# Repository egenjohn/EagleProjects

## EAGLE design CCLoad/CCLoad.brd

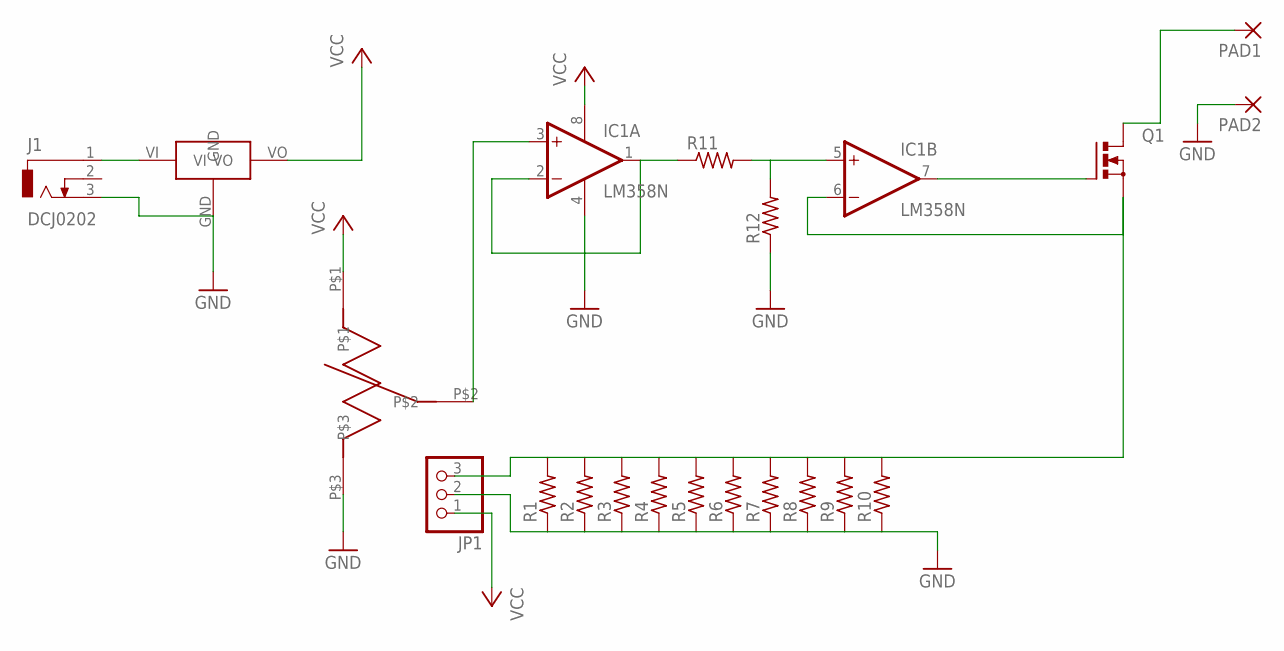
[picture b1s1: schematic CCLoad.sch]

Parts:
IC1: LM358N; DIL08
J1: DCJ0202
JP1: PINHD-1X3; 1X03
PAD1, PAD2: 3,17/1,3
Q1: PMOSFET_NTO220BV; TO220BV
R1, R2, R3, R4, R5, R6, R7, R8, R9, R10, R11, R12: R-US_0207/10; 0207/10
U$1: 3590
U$3: 7805-TO220V; TO220AV

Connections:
GND: IC1.4 (V-), J1.3, JP1.2, PAD2.1, R1.1, R2.1, R3.1, R4.1, R5.1, R6.1, R7.1, R8.1, R9.1, R10.1, R12.1, U$1.P$3, U$3.GND
unnamed: IC1.1 (OUT), IC1.2 (-IN), R11.1
unnamed: IC1.5 (+IN), R11.2, R12.2
unnamed: IC1.7 (OUT), Q1.G
unnamed: IC1.6 (-IN), JP1.3, Q1.S, R1.2, R2.2, R3.2, R4.2, R5.2, R6.2, R7.2, R8.2, R9.2, R10.2
unnamed: PAD1.1, Q1.D
unnamed: J1.1, U$3.VI
unnamed: IC1.3 (+IN), U$1.P$2
VCC: IC1.8 (V+), JP1.1, U$1.P$1, U$3.VO

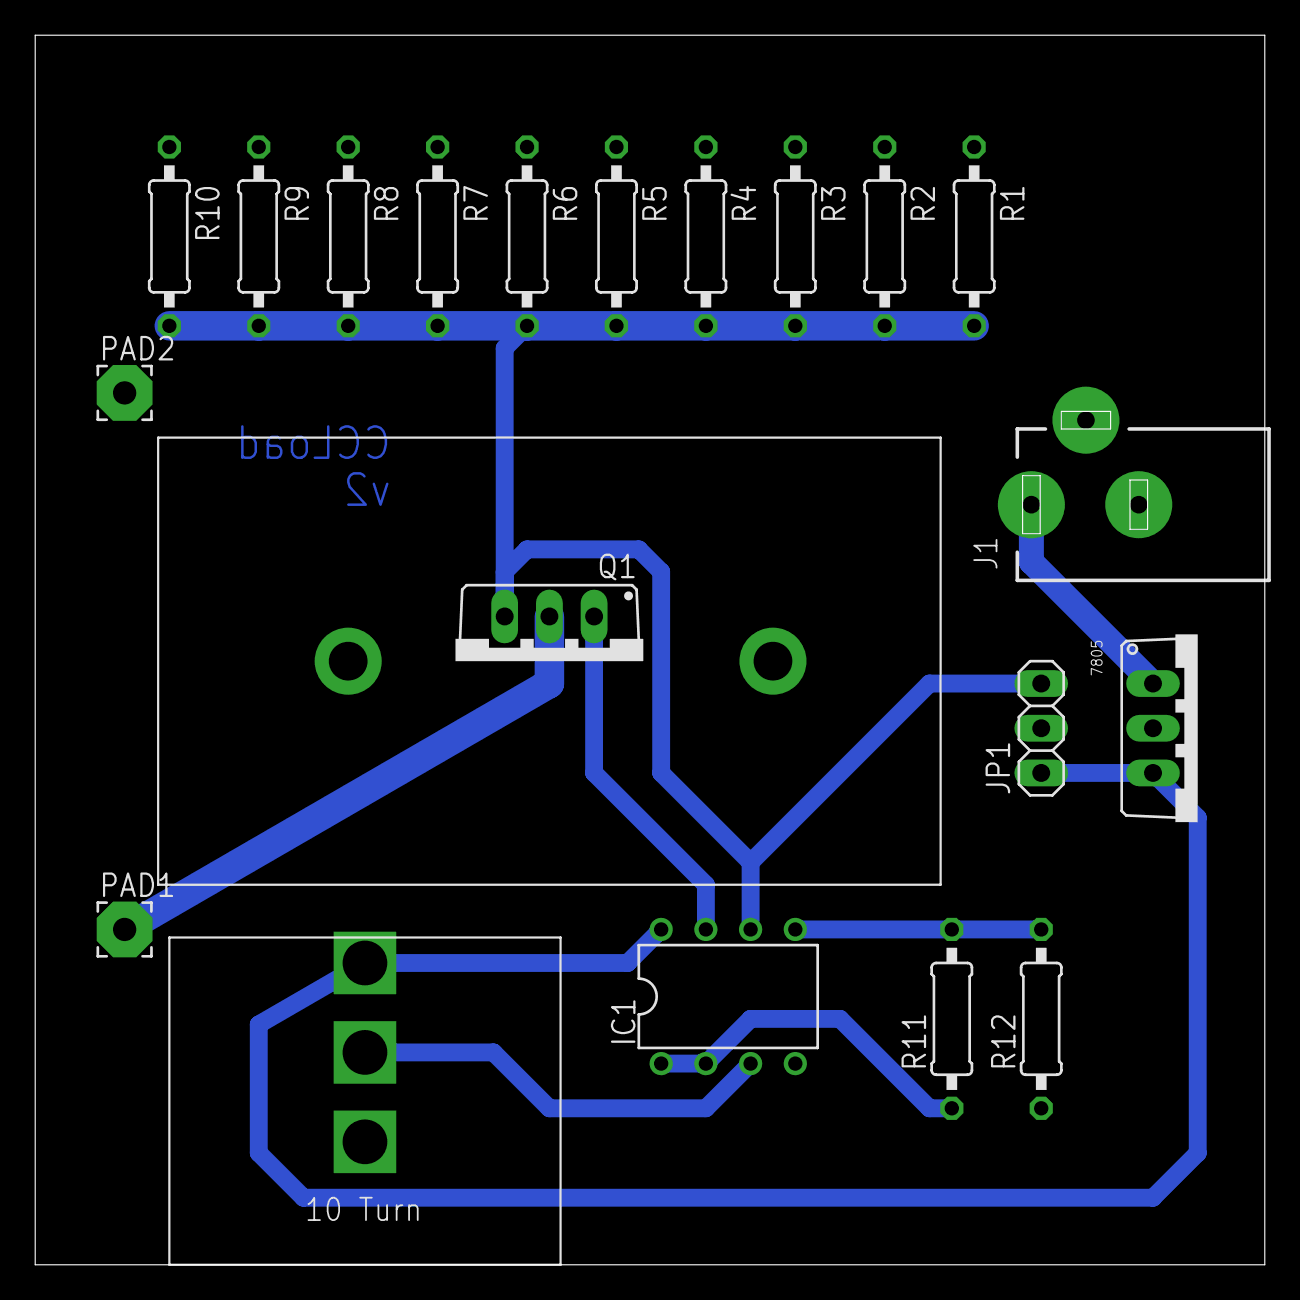
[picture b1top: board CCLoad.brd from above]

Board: 2 copper layers, 69.8 x 69.8 mm, 20 parts (0 on the bottom side), 9 nets.

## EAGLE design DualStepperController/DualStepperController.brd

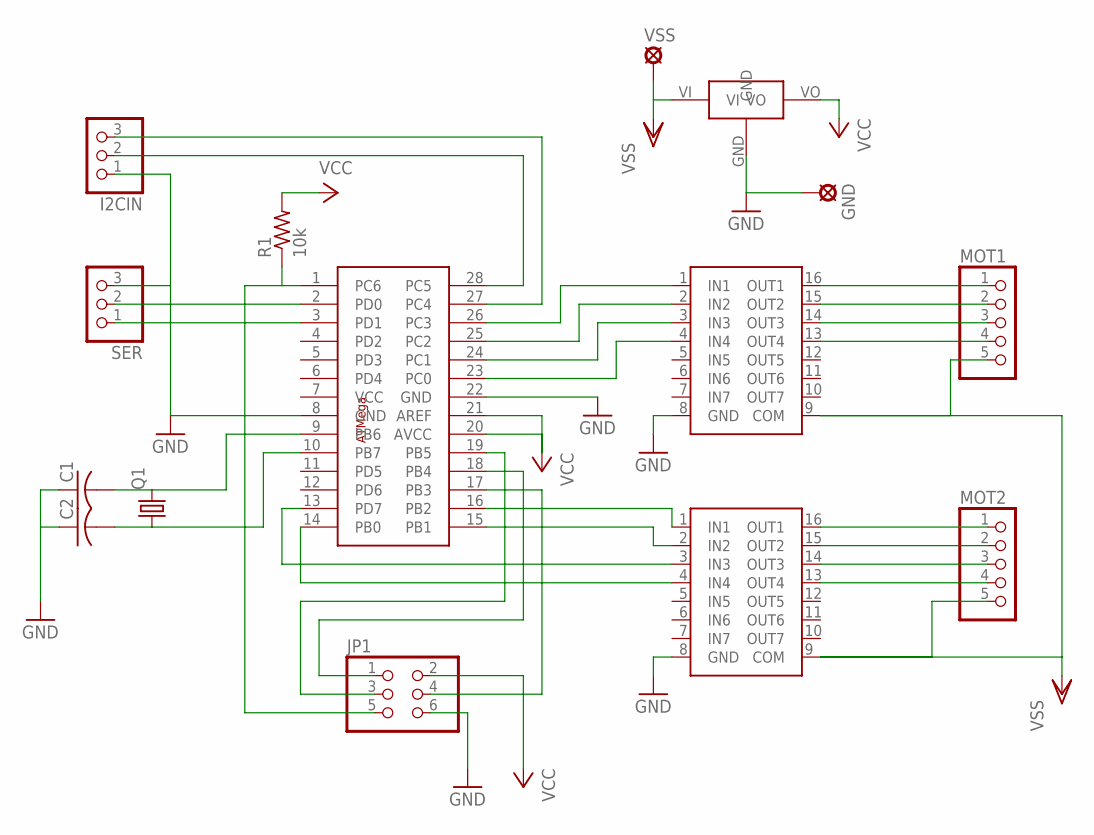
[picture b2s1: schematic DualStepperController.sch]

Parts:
C1, C2: C-US025-024X044; C025-024X044
GND: SE14
I2CIN: PINHD-1X3; 1X03
JP1: PINHD-2X3; 2X03
MOT1, MOT2: PINHD-1X5; 1X05
Q1: CRYSTALHC49S; HC49/S
R1: 10k; 0207/7
SER: PINHD-1X3; 1X03
U$1: ATMEGA328P; ATMEGA328P-DIP
U$2, U$3: ULN2003; DIP16
U$4: 7805-TO220V; TO220AV
VSS: SE14

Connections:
GND: C1.1, C2.1, GND.MP, I2CIN.1, JP1.6, SER.3, U$1.8 (GND), U$1.22 (GND), U$2.8 (GND), U$3.8 (GND), U$4.GND
unnamed: MOT1.1, U$2.16 (OUT1)
unnamed: MOT1.2, U$2.15 (OUT2)
unnamed: MOT1.3, U$2.14 (OUT3)
unnamed: MOT1.4, U$2.13 (OUT4)
unnamed: I2CIN.2, U$1.28 (PC5)
unnamed: I2CIN.3, U$1.27 (PC4)
unnamed: MOT2.1, U$3.16 (OUT1)
unnamed: MOT2.2, U$3.15 (OUT2)
unnamed: MOT2.3, U$3.14 (OUT3)
unnamed: MOT2.4, U$3.13 (OUT4)
unnamed: C1.2, Q1.2, U$1.9 (PB6)
unnamed: C2.2, Q1.1, U$1.10 (PB7)
unnamed: SER.1, U$1.3 (PD1)
unnamed: JP1.5, R1.1, U$1.1 (PC6)
unnamed: JP1.1, U$1.18 (PB4)
unnamed: JP1.3, U$1.19 (PB5)
unnamed: JP1.4, U$1.17 (PB3)
unnamed: U$1.26 (PC3), U$2.1 (IN1)
unnamed: U$1.25 (PC2), U$2.2 (IN2)
unnamed: U$1.24 (PC1), U$2.3 (IN3)
unnamed: U$1.23 (PC0), U$2.4 (IN4)
unnamed: U$1.16 (PB2), U$3.1 (IN1)
unnamed: U$1.15 (PB1), U$3.2 (IN2)
unnamed: U$1.14 (PB0), U$3.4 (IN4)
unnamed: U$1.13 (PD7), U$3.3 (IN3)
unnamed: SER.2, U$1.2 (PD0)
VCC: JP1.2, R1.2, U$1.20 (AVCC), U$1.21 (AREF), U$4.VO
VSS: MOT1.5, MOT2.5, U$2.9 (COM), U$3.9 (COM), U$4.VI, VSS.MP

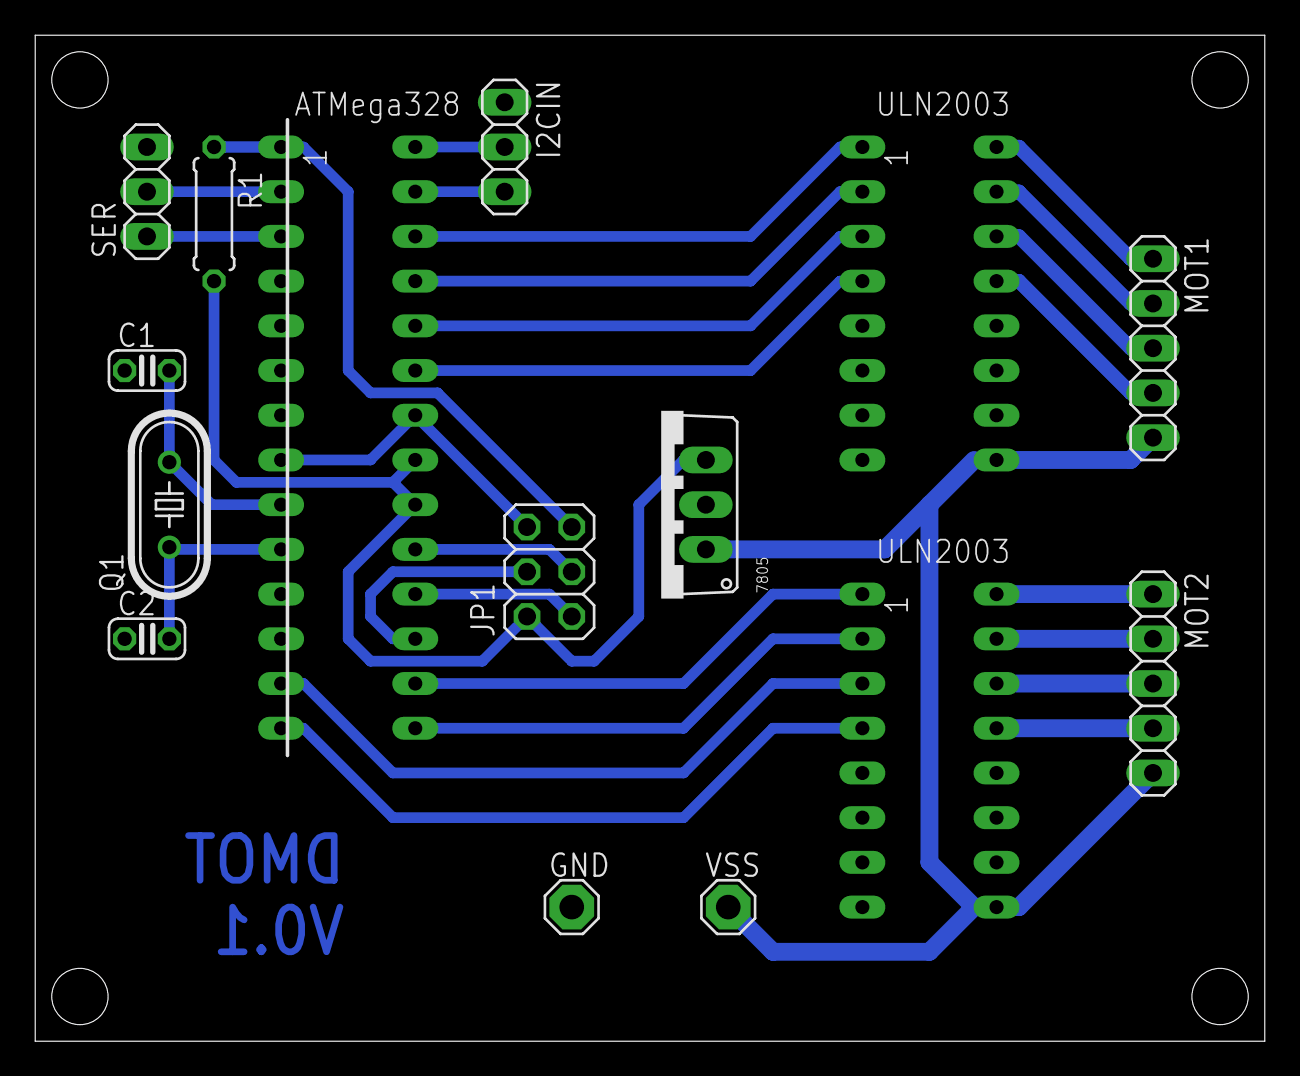
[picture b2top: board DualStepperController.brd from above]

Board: 2 copper layers, 69.8 x 57.1 mm, 15 parts (0 on the bottom side), 29 nets.

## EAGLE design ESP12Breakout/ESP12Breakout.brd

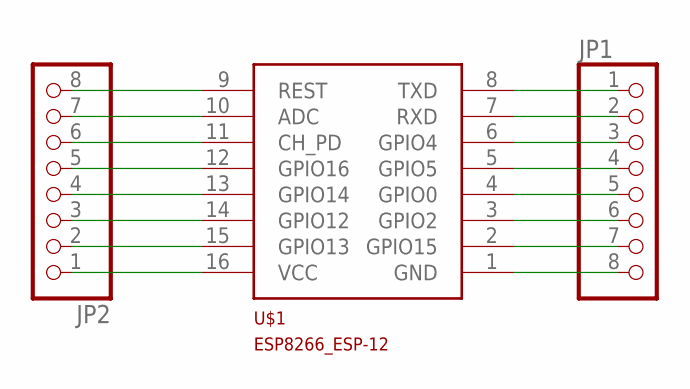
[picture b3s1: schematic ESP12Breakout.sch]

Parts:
JP1, JP2: PINHD-1X8; 1X08
U$1: ESP8266_ESP-12; ESP8266-ESP12

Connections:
unnamed: JP1.1, U$1.8 (TXD)
unnamed: JP1.2, U$1.7 (RXD)
unnamed: JP1.3, U$1.6 (GPIO4)
unnamed: JP1.4, U$1.5 (GPIO5)
unnamed: JP1.5, U$1.4 (GPIO0)
unnamed: JP1.6, U$1.3 (GPIO2)
unnamed: JP1.7, U$1.2 (GPIO15)
unnamed: JP1.8, U$1.1 (GND)
unnamed: JP2.8, U$1.9 (REST)
unnamed: JP2.7, U$1.10 (ADC)
unnamed: JP2.6, U$1.11 (CH_PD)
unnamed: JP2.5, U$1.12 (GPIO16)
unnamed: JP2.4, U$1.13 (GPIO14)
unnamed: JP2.3, U$1.14 (GPIO12)
unnamed: JP2.2, U$1.15 (GPIO13)
unnamed: JP2.1, U$1.16 (VCC)

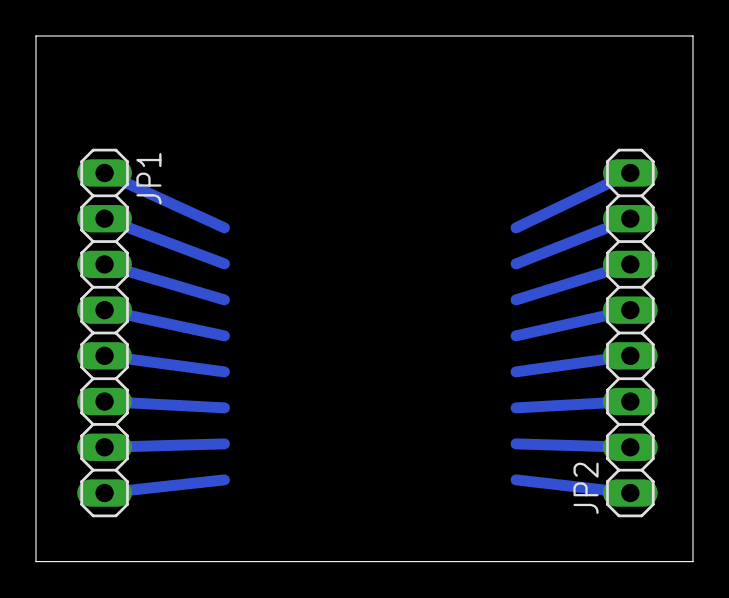
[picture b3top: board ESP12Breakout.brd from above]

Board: 2 copper layers, 36.5 x 29.2 mm, 3 parts (1 on the bottom side), 16 nets.

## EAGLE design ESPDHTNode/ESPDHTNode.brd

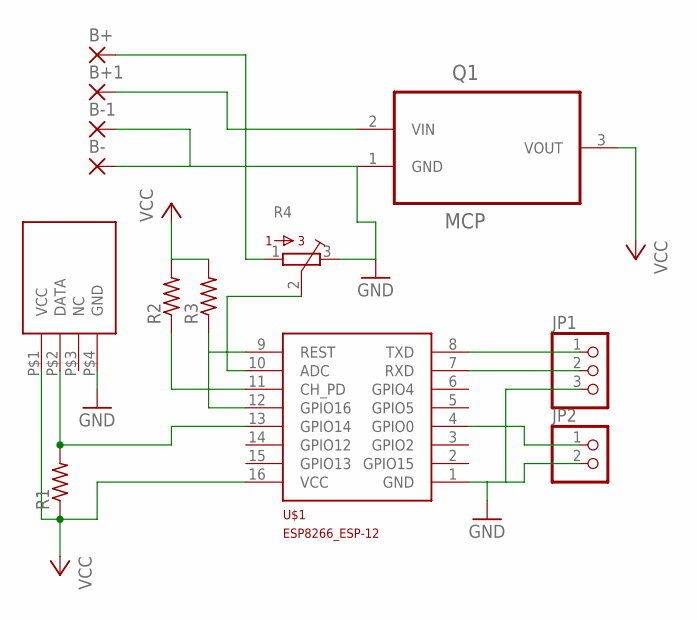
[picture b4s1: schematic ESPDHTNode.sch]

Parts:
B+, B+1: WIREPAD2,54/0,8; 2,54/0,8
B-, B-1: WIREPAD2,54/0,8; 2,54/0,8
JP1: PINHD-1X3; 1X03
JP2: PINHD-1X2; 1X02
Q1: MCP; TO127P254X533-3
R1, R2, R3: R-US_0207/10; 0207/10
R4: 3362P
U$1: ESP8266_ESP-12; ESP8266-ESP12
U$2: DHTDHT11; DHT

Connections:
GND: B-.1, B-1.1, JP1.3, JP2.2, Q1.1 (GND), R4.3, U$1.1 (GND), U$2.P$4 (GND)
unnamed: R1.2, U$1.13 (GPIO14), U$2.P$2 (DATA)
unnamed: JP1.1, U$1.8 (TXD)
unnamed: JP1.2, U$1.7 (RXD)
unnamed: R3.1, U$1.9 (REST), U$1.12 (GPIO16)
unnamed: R2.1, U$1.11 (CH_PD)
unnamed: B+.1, B+1.1, Q1.2 (VIN), R4.1
unnamed: JP2.1, U$1.4 (GPIO0)
unnamed: R4.2, U$1.10 (ADC)
VCC: Q1.3 (VOUT), R1.1, R2.2, R3.2, U$1.16 (VCC), U$2.P$1 (VCC)

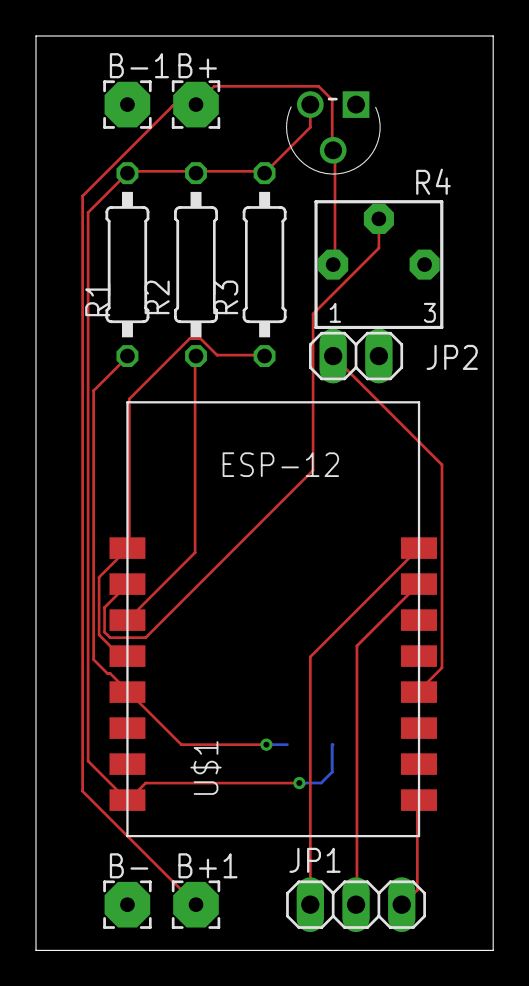
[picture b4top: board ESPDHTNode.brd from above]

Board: 2 copper layers, 25.4 x 50.8 mm, 13 parts (1 on the bottom side), 10 nets.

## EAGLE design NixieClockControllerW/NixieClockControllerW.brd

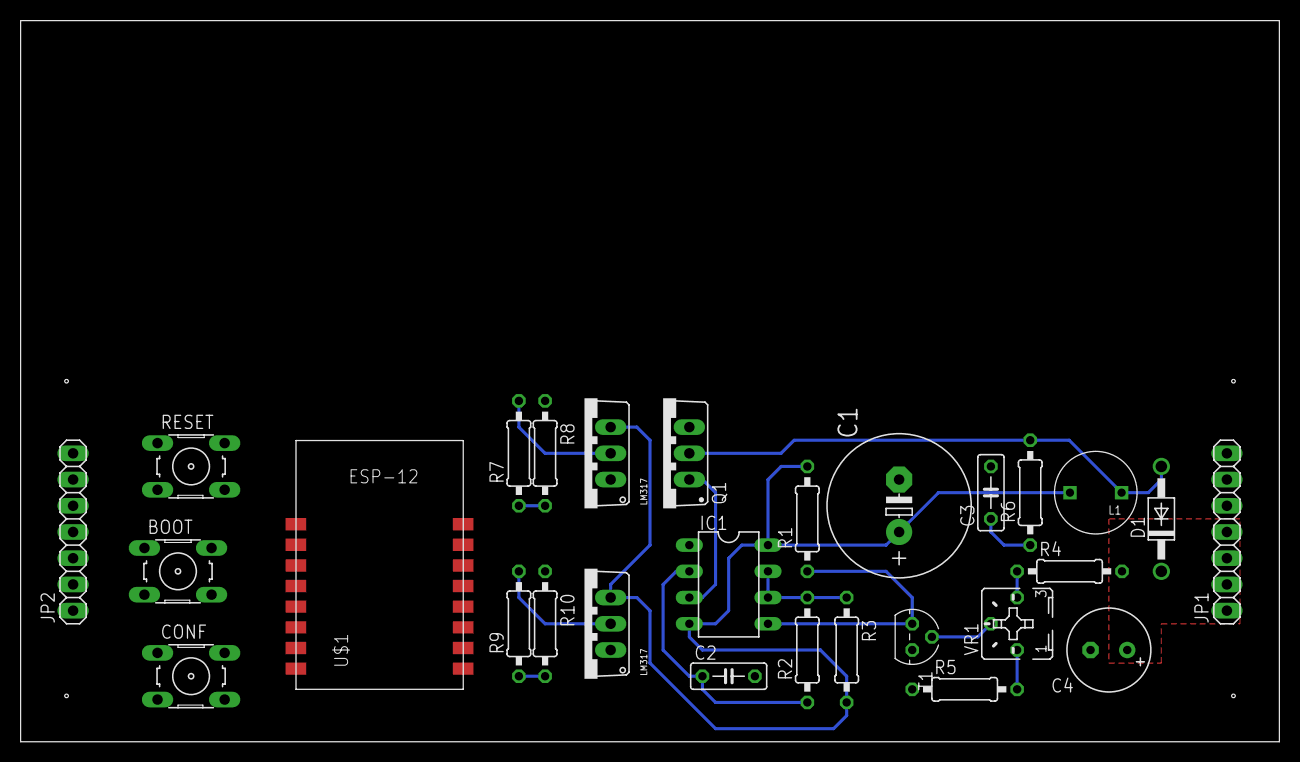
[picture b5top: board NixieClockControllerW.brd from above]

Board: 2 copper layers, 121.9 x 69.8 mm, 28 parts (0 on the bottom side), 16 nets.

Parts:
BOOT: B3F-10XX
C1: 470u; E5-13
C2: 2n2; C050-025X075
C3: 100pF; C050-025X075
C4: 4u7; E3,5-8
CONF: B3F-10XX
D1: 1N4942; DO41-10
IC1: NE555; DIL-08
JP1, JP2: 1X07
L1: 100uH; RLB0914
Q1: BUZ11BV; TO220BV
R1: 56k; 0207/10
R2: 10k; 0207/10
R3: 1k; 0207/10
R4, R8: 470; 0207/10
R5: 220k; 0207/10
R6: 2k2; 0207/10
R7: 270; 0207/10
R9: 220; 0207/10
R10: 680; 0207/10
RESET: B3F-10XX
T1: BC547; TO92
U$1: ESP8266_ESP-12; ESP8266-ESP12
U$2, U$3: LM317-TO220; LM317-TO220AV
VR1: B25P

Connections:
3V3: R7.2, U$2.OUT
5V: R9.2, U$3.OUT
GND: C1.-, C2.2, C3.2, C4.-, IC1.1, JP1.5, JP1.6, JP1.7, Q1.S, R5.1, R8.1, R10.1, T1.1, U$2.ADJ, U$3.ADJ
HV: C4.+, D1.C, JP1.1, JP1.2, JP1.3, JP1.4, R4.2
unnamed: IC1.3, Q1.G
unnamed: D1.A, L1.1, Q1.D, R6.2
unnamed: IC1.6, IC1.7, R2.2, R3.1
unnamed: R4.1, VR1.E
unnamed: IC1.5, R1.1, T1.3
unnamed: R5.2, VR1.A
unnamed: T1.2, VR1.S
unnamed: C3.1, R6.1
unnamed: C2.1, IC1.2, R2.1
unnamed: R7.1, R8.2
unnamed: R9.1, R10.2
VCC: C1.+, IC1.4, IC1.8, L1.2, R1.2, R3.2, U$2.IN, U$3.IN

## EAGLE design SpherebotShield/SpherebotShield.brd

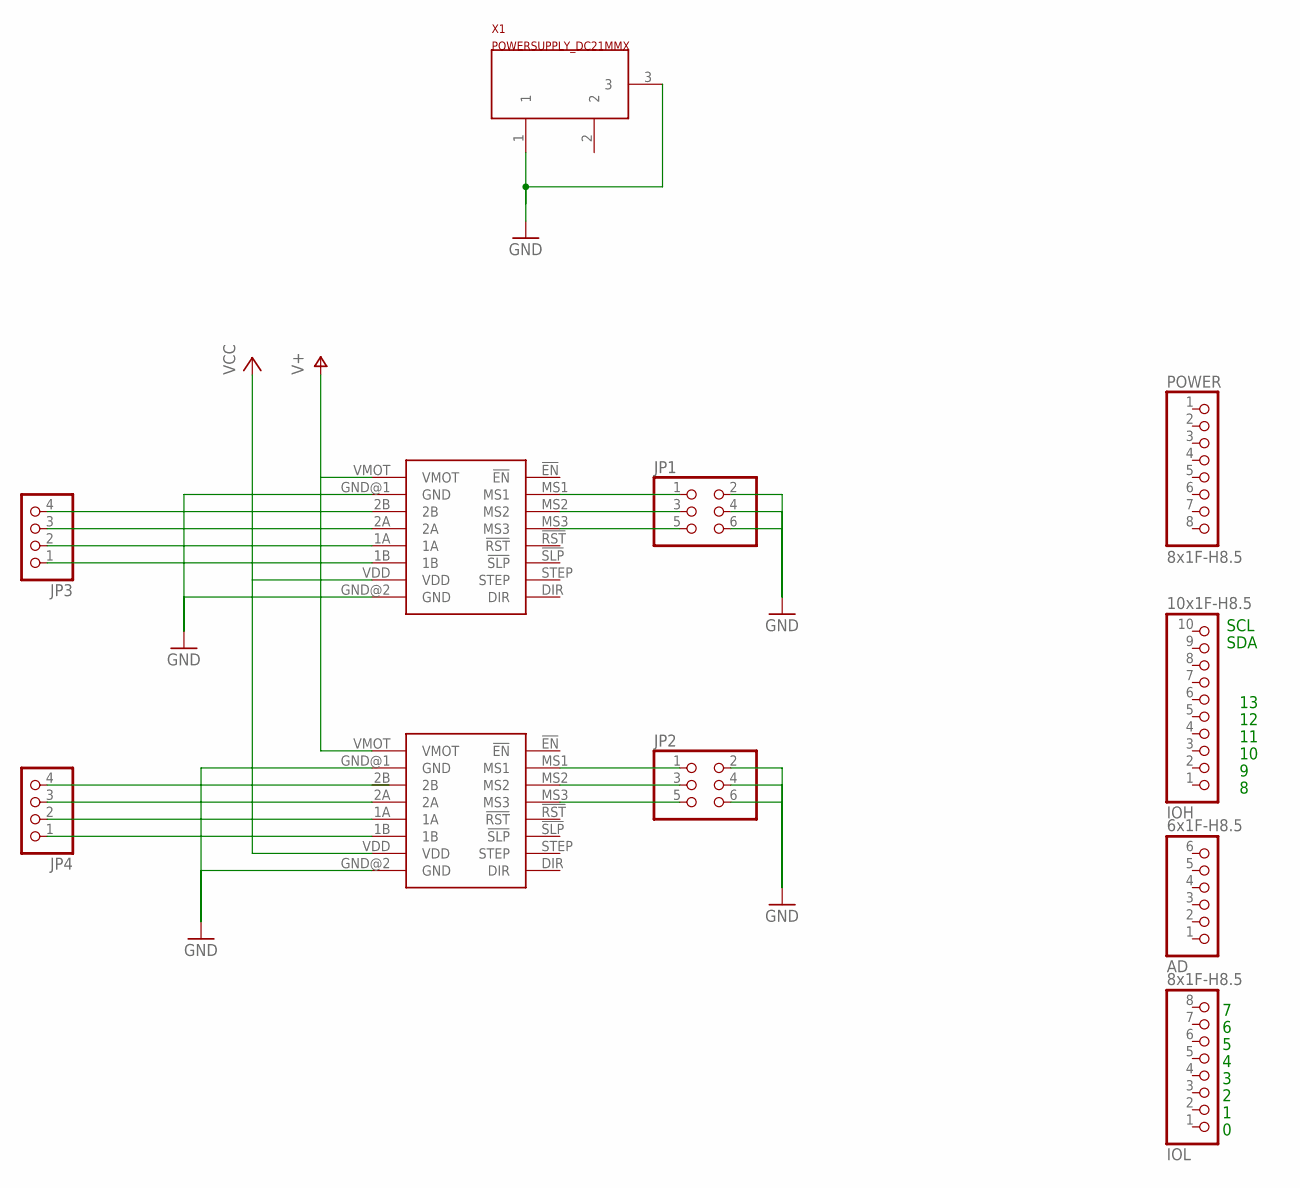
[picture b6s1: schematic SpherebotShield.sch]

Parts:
AD: 6x1F-H8.5; 1X06
IOH: 10x1F-H8.5; 1X10
IOL: 8x1F-H8.5; 1X08
JP1, JP2: PINHD-2X3; 2X03
JP3, JP4: PINHD-1X4; 1X04
POWER: 8x1F-H8.5; 1X08
U$1, U$2: STEPSTICK
X1: POWERSUPPLY_DC21MMX; POWERSUPPLY_DC-21MM

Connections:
2: X1.2
GND: JP1.2, JP1.4, JP1.6, JP2.2, JP2.4, JP2.6, U$1.GND@1 (GND), U$1.GND@2 (GND), U$2.GND@1 (GND), U$2.GND@2 (GND), X1.1, X1.3
unnamed: JP1.1, U$1.MS1
unnamed: JP1.3, U$1.MS2
unnamed: JP1.5, U$1.MS3
unnamed: JP2.1, U$2.MS1
unnamed: JP2.3, U$2.MS2
unnamed: JP2.5, U$2.MS3
unnamed: JP3.4, U$1.2B
unnamed: JP3.3, U$1.2A
unnamed: JP3.2, U$1.1A
unnamed: JP3.1, U$1.1B
unnamed: JP4.3, U$2.2A
unnamed: JP4.2, U$2.1A
unnamed: JP4.1, U$2.1B
V+: U$1.VMOT, U$2.VMOT
VCC: U$1.VDD, U$2.VDD

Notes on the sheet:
SDA
SCL

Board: 2 copper layers, 11 parts (0 on the bottom side), 16 nets, no tracks yet.
